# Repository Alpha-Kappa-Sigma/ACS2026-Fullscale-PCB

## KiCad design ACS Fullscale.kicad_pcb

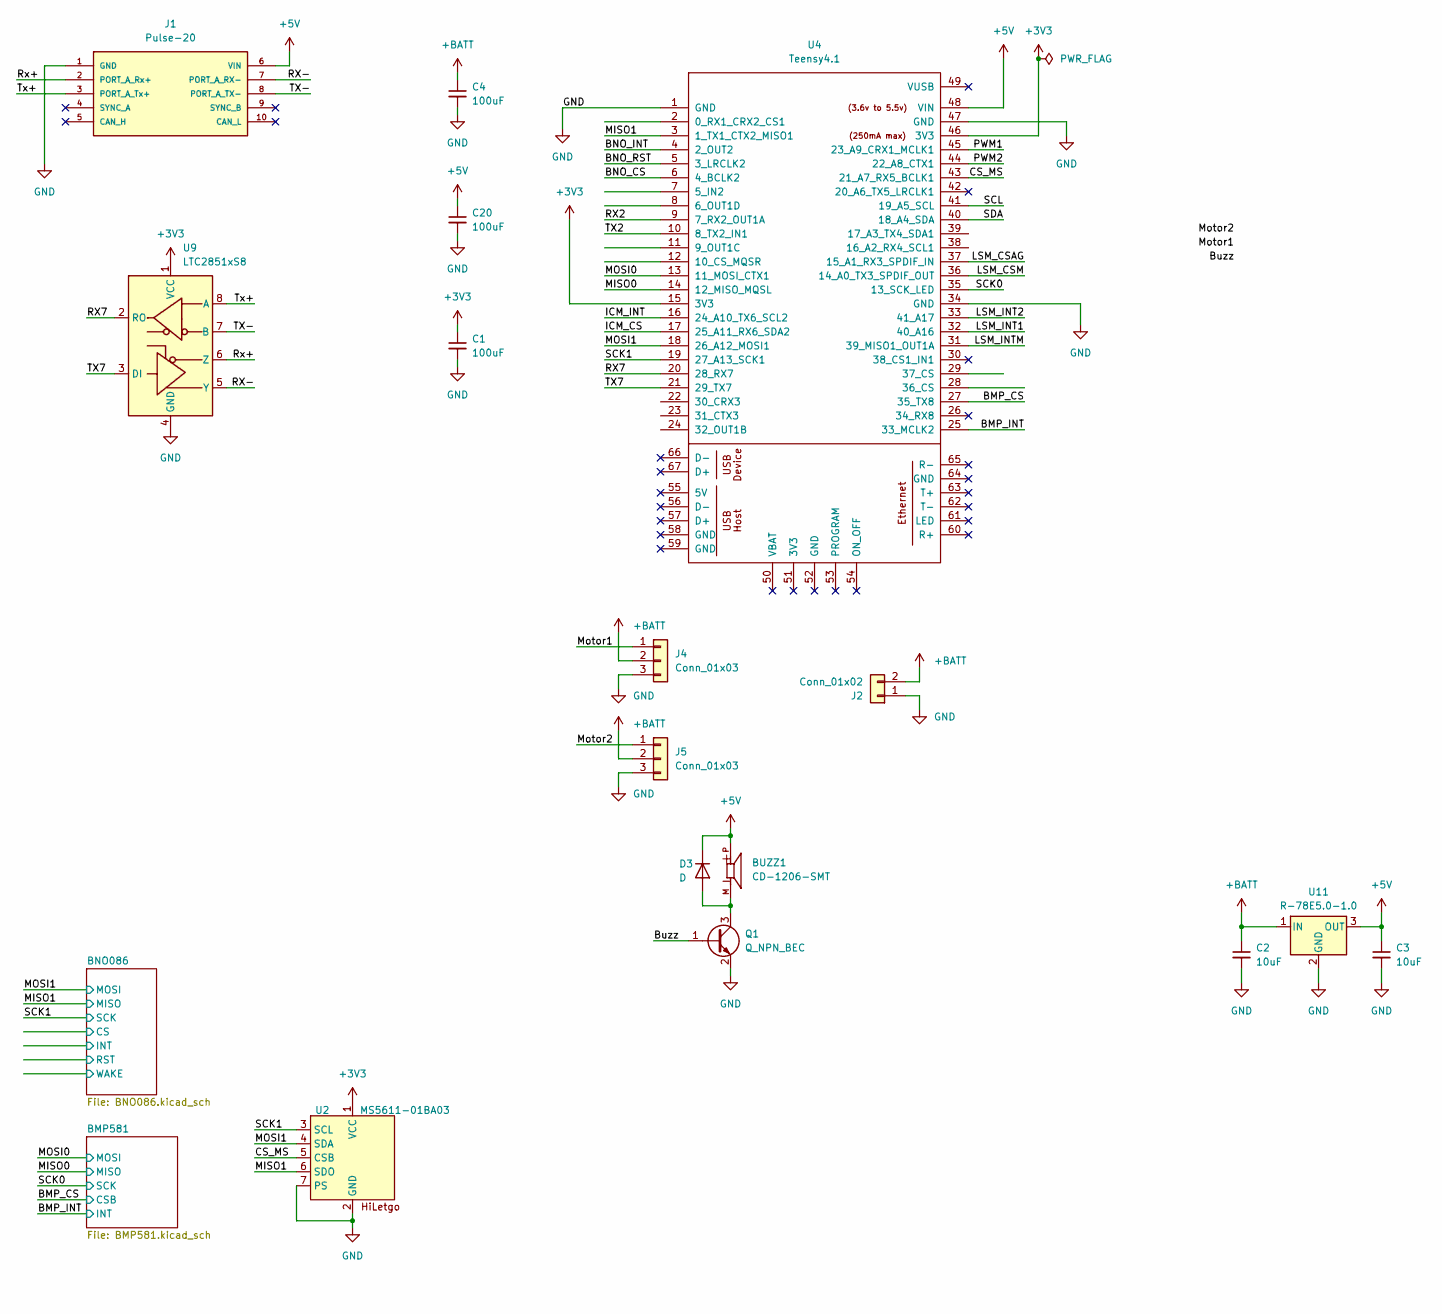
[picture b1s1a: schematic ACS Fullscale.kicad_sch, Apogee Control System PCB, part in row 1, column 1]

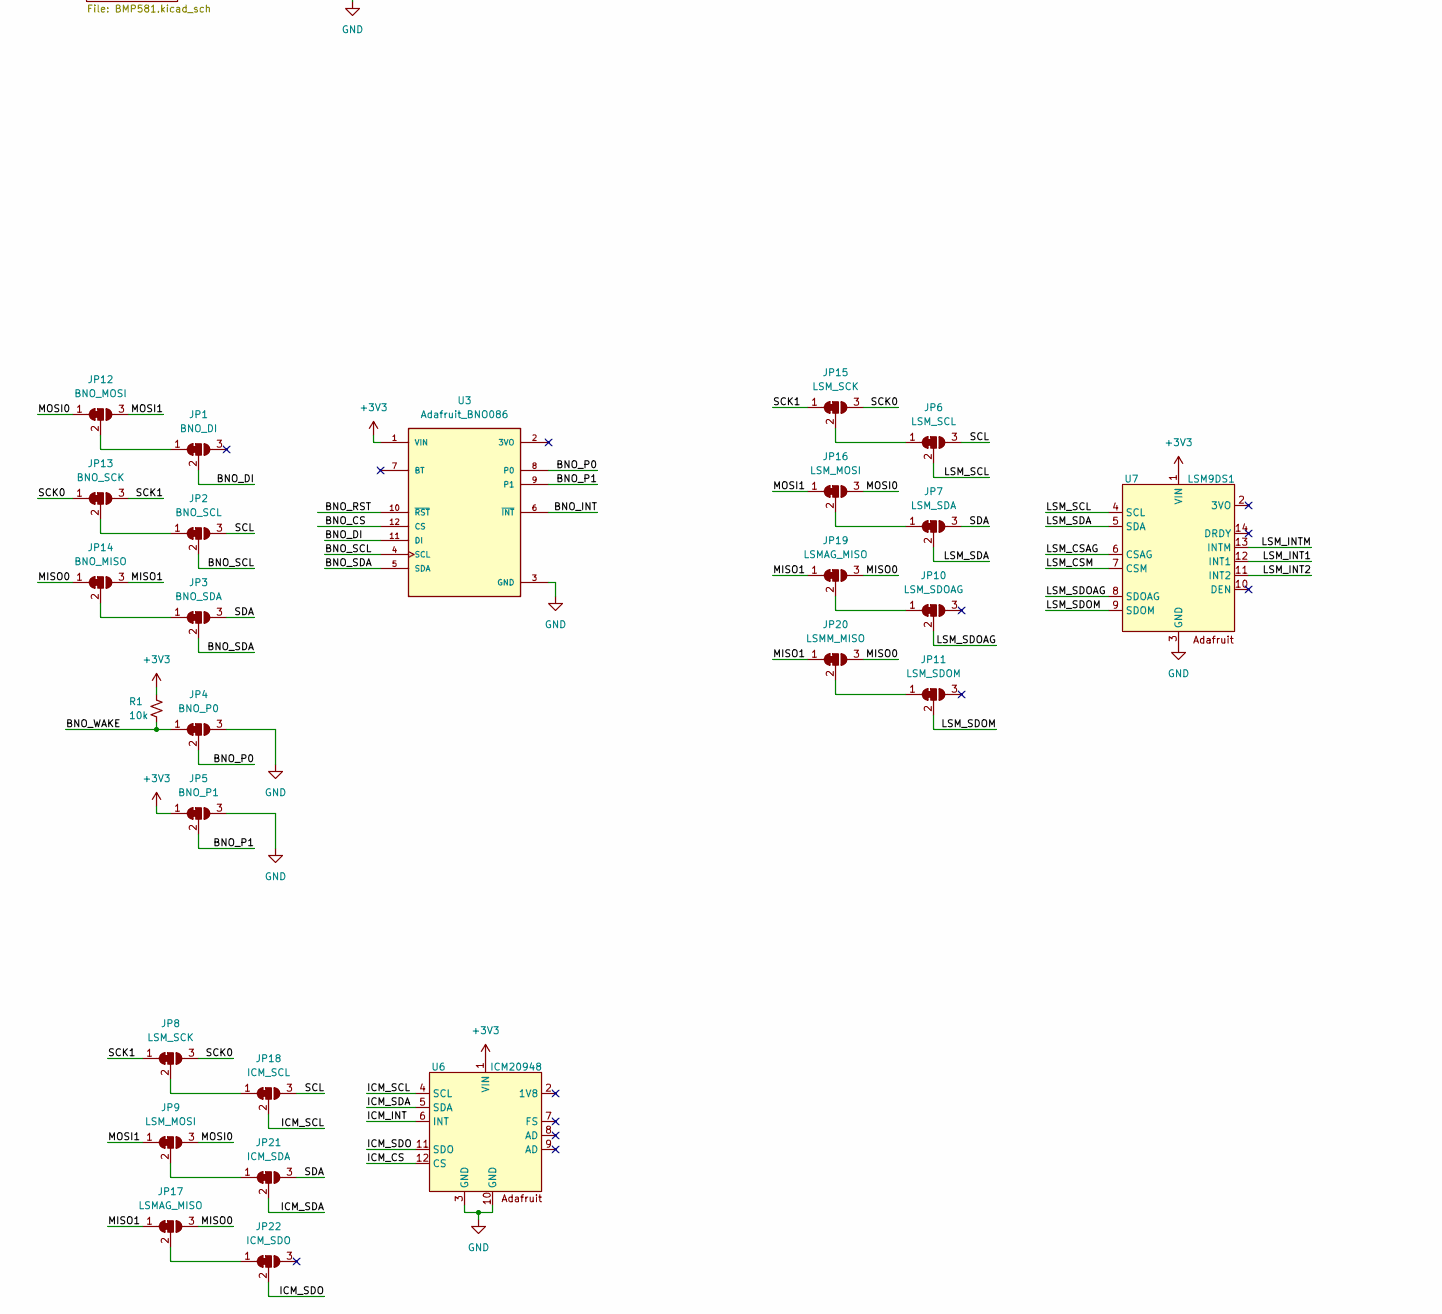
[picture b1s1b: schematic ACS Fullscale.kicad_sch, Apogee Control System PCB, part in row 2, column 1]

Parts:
BUZZ1: CD-1206-SMT; CUI_CD-1206-SMT; DigiKey_Part_Number 102-1150-ND
C1, C4, C20: 100uF; C_1206_3216Metric
C2, C3: 10uF; C_0603_1608Metric
D3: D; D_SOD-323
J1: Pulse-20
J2: Conn_01x02; AMASS_XT30U-M_1x02_P5.0mm_Vertical
J4, J5: Conn_01x03; PinHeader_1x03_P2.54mm_Vertical
JP1: BNO_DI; SolderJumper-3_P1.3mm_Bridged2Bar12_RoundedPad1.0x1.5mm
JP2: BNO_SCL; SolderJumper-3_P1.3mm_Bridged2Bar12_RoundedPad1.0x1.5mm
JP3: BNO_SDA; SolderJumper-3_P1.3mm_Bridged2Bar12_RoundedPad1.0x1.5mm
JP4: BNO_P0; SolderJumper-3_P1.3mm_Bridged2Bar12_RoundedPad1.0x1.5mm
JP5: BNO_P1; SolderJumper-3_P1.3mm_Bridged2Bar12_RoundedPad1.0x1.5mm
JP6: LSM_SCL; SolderJumper-3_P1.3mm_Bridged2Bar12_RoundedPad1.0x1.5mm
JP7: LSM_SDA; SolderJumper-3_P1.3mm_Bridged2Bar12_RoundedPad1.0x1.5mm
JP8, JP15: LSM_SCK; SolderJumper-3_P1.3mm_Bridged2Bar12_RoundedPad1.0x1.5mm
JP9, JP16: LSM_MOSI; SolderJumper-3_P1.3mm_Bridged2Bar12_RoundedPad1.0x1.5mm
JP10: LSM_SDOAG; SolderJumper-3_P1.3mm_Bridged2Bar12_RoundedPad1.0x1.5mm
JP11: LSM_SDOM; SolderJumper-3_P1.3mm_Bridged2Bar12_RoundedPad1.0x1.5mm
JP12: BNO_MOSI; SolderJumper-3_P1.3mm_Bridged2Bar12_RoundedPad1.0x1.5mm
JP13: BNO_SCK; SolderJumper-3_P1.3mm_Bridged2Bar12_RoundedPad1.0x1.5mm
JP14: BNO_MISO; SolderJumper-3_P1.3mm_Bridged2Bar12_RoundedPad1.0x1.5mm
JP17, JP19: LSMAG_MISO; SolderJumper-3_P1.3mm_Bridged2Bar12_RoundedPad1.0x1.5mm
JP18: ICM_SCL; SolderJumper-3_P1.3mm_Bridged2Bar12_RoundedPad1.0x1.5mm
JP20: LSMM_MISO; SolderJumper-3_P1.3mm_Bridged2Bar12_RoundedPad1.0x1.5mm
JP21: ICM_SDA; SolderJumper-3_P1.3mm_Bridged2Bar12_RoundedPad1.0x1.5mm
JP22: ICM_SDO; SolderJumper-3_P1.3mm_Bridged2Bar12_RoundedPad1.0x1.5mm
Q1: Q_NPN_BEC; TSOT-23
R1: 10k; R_0805_2012Metric_Pad1.20x1.40mm_HandSolder
U2: MS5611-01BA03; HiLetgo MS5611
U3: Adafruit_BNO086; Adafruit BNO086; PARTREV 2021-03-16
U4: Teensy4.1; Teensy41
U6: ICM20948; Adafruit ICM20948
U7: LSM9DS1; Adafruit LSM9DS1
U9: LTC2851xS8; SOIC-8_3.9x4.9mm_P1.27mm
U11: R-78E5.0-1.0; Converter_DCDC_RECOM_R-78E-0.5_THT

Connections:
+3V3: C1.1, JP5.1 (A), R1.2, U2.1 (VCC), U3.1 (VIN), U4.15 (3V3), U4.46 (3V3), U6.1 (VIN), U7.1 (VIN), U9.1 (VCC); also elsewhere on the board
+5V: BUZZ1.P, C3.1, C20.1, D3.1 (K), J1.6 (VIN), U4.48 (VIN), U11.3 (OUT)
+BATT: C2.1, C4.1, J2.2, J4.2, J5.2, U11.1 (IN)
/BMP_CS: U4.27 (35_TX8); also elsewhere on the board
/BMP_INT: U4.25 (33_MCLK2); also elsewhere on the board
/BNO_CS: U3.12 (CS), U4.6 (4_BCLK2)
/BNO_DI: JP1.2 (C), U3.11 (DI)
/BNO_INT: U3.6 (~INT), U4.4 (2_OUT2)
/BNO_P0: JP4.2 (C), U3.8 (P0)
/BNO_P1: JP5.2 (C), U3.9 (P1)
/BNO_RST: U3.10 (~RST), U4.5 (3_LRCLK2)
/BNO_SCL: JP2.2 (C), U3.4 (SCL)
/BNO_SDA: JP3.2 (C), U3.5 (SDA)
/BNO_WAKE: JP4.1 (A), R1.1
/Buzz: Q1.1 (B)
/CS_MS: U2.5 (CSB), U4.43 (21_A7_RX5_BCLK1)
/ICM_CS: U4.17 (25_A11_RX6_SDA2), U6.12 (CS)
/ICM_INT: U4.16 (24_A10_TX6_SCL2), U6.6 (INT)
/ICM_SCL: JP18.2 (C), U6.4 (SCL)
/ICM_SDA: JP21.2 (C), U6.5 (SDA)
/ICM_SDO: JP22.2 (C), U6.11 (SDO)
/LSM_CSAG: U4.37 (15_A1_RX3_SPDIF_IN), U7.6 (CSAG)
/LSM_CSM: U4.36 (14_A0_TX3_SPDIF_OUT), U7.7 (CSM)
/LSM_INT1: U4.32 (40_A16), U7.12 (INT1)
/LSM_INT2: U4.33 (41_A17), U7.11 (INT2)
/LSM_INTM: U4.31 (39_MISO1_OUT1A), U7.13 (INTM)
/LSM_SCL: JP6.2 (C), U7.4 (SCL)
/LSM_SDA: JP7.2 (C), U7.5 (SDA)
/LSM_SDOAG: JP10.2 (C), U7.8 (SDOAG)
/LSM_SDOM: JP11.2 (C), U7.9 (SDOM)
/MISO0: JP14.1 (A), JP17.3 (B), JP19.3 (B), JP20.3 (B), U4.14 (12_MISO_MQSL); also elsewhere on the board
/MISO1: JP14.3 (B), JP17.1 (A), JP19.1 (A), JP20.1 (A), U2.6 (SDO), U4.3 (1_TX1_CTX2_MISO1)
/MOSI0: JP9.3 (B), JP12.1 (A), JP16.3 (B), U4.13 (11_MOSI_CTX1); also elsewhere on the board
/MOSI1: JP9.1 (A), JP12.3 (B), JP16.1 (A), U2.4 (SDA), U4.18 (26_A12_MOSI1)
/Motor1: J4.1
/Motor2: J5.1
/PWM1: U4.45 (23_A9_CRX1_MCLK1)
/PWM2: U4.44 (22_A8_CTX1)
/RX2: U4.9 (7_RX2_OUT1A)
/RX7: U4.20 (28_RX7), U9.2 (RO)
/RX-: J1.7 (PORT_A_RX-), U9.5 (Y)
/Rx+: J1.2 (PORT_A_Rx+), U9.6 (Z)
/SCK0: JP8.3 (B), JP13.1 (A), JP15.3 (B), U4.35 (13_SCK_LED); also elsewhere on the board
/SCK1: JP8.1 (A), JP13.3 (B), JP15.1 (A), U2.3 (SCL), U4.19 (27_A13_SCK1)
/SCL: JP2.3 (B), JP6.3 (B), JP18.3 (B), U4.41 (19_A5_SCL)
/SDA: JP3.3 (B), JP7.3 (B), JP21.3 (B), U4.40 (18_A4_SDA)
/TX2: U4.10 (8_TX2_IN1)
/TX7: U4.21 (29_TX7), U9.3 (DI)
/TX-: J1.8 (PORT_A_TX-), U9.7 (B)
/Tx+: J1.3 (PORT_A_Tx+), U9.8 (A)
GND: C1.2, C2.2, C3.2, C4.2, C20.2, J1.1 (GND), J2.1, J4.3, J5.3, JP4.3 (B), JP5.3 (B), Q1.2 (E), U2.2 (GND), U2.7 (PS), U3.3 (GND), U4.1 (GND), U4.34 (GND), U4.47 (GND), U6.3 (GND), U6.10 (GND), U7.3 (GND), U9.4 (GND), U11.2 (GND); also elsewhere on the board
unnamed: BUZZ1.M, D3.2 (A), Q1.3 (C)
unnamed: JP1.1 (A), JP12.2 (C)
unnamed: JP10.1 (A), JP19.2 (C)
unnamed: JP11.1 (A), JP20.2 (C)
unnamed: JP2.1 (A), JP13.2 (C)
unnamed: JP3.1 (A), JP14.2 (C)
unnamed: JP6.1 (A), JP15.2 (C)
unnamed: JP7.1 (A), JP16.2 (C)
unnamed: JP17.2 (C), JP22.1 (A)
unnamed: JP8.2 (C), JP18.1 (A)
unnamed: JP9.2 (C), JP21.1 (A)

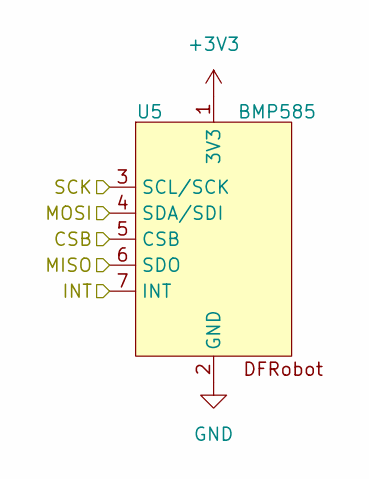
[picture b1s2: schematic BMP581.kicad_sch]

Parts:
U5: BMP585; DFRobot BMP585

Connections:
+3V3: U5.1 (3V3); also elsewhere on the board
/BMP_CS: U5.5 (CSB); also elsewhere on the board
/BMP_INT: U5.7 (INT); also elsewhere on the board
/MISO0: U5.6 (SDO); also elsewhere on the board
/MOSI0: U5.4 (SDA/SDI); also elsewhere on the board
/SCK0: U5.3 (SCL/SCK); also elsewhere on the board
GND: U5.2 (GND); also elsewhere on the board

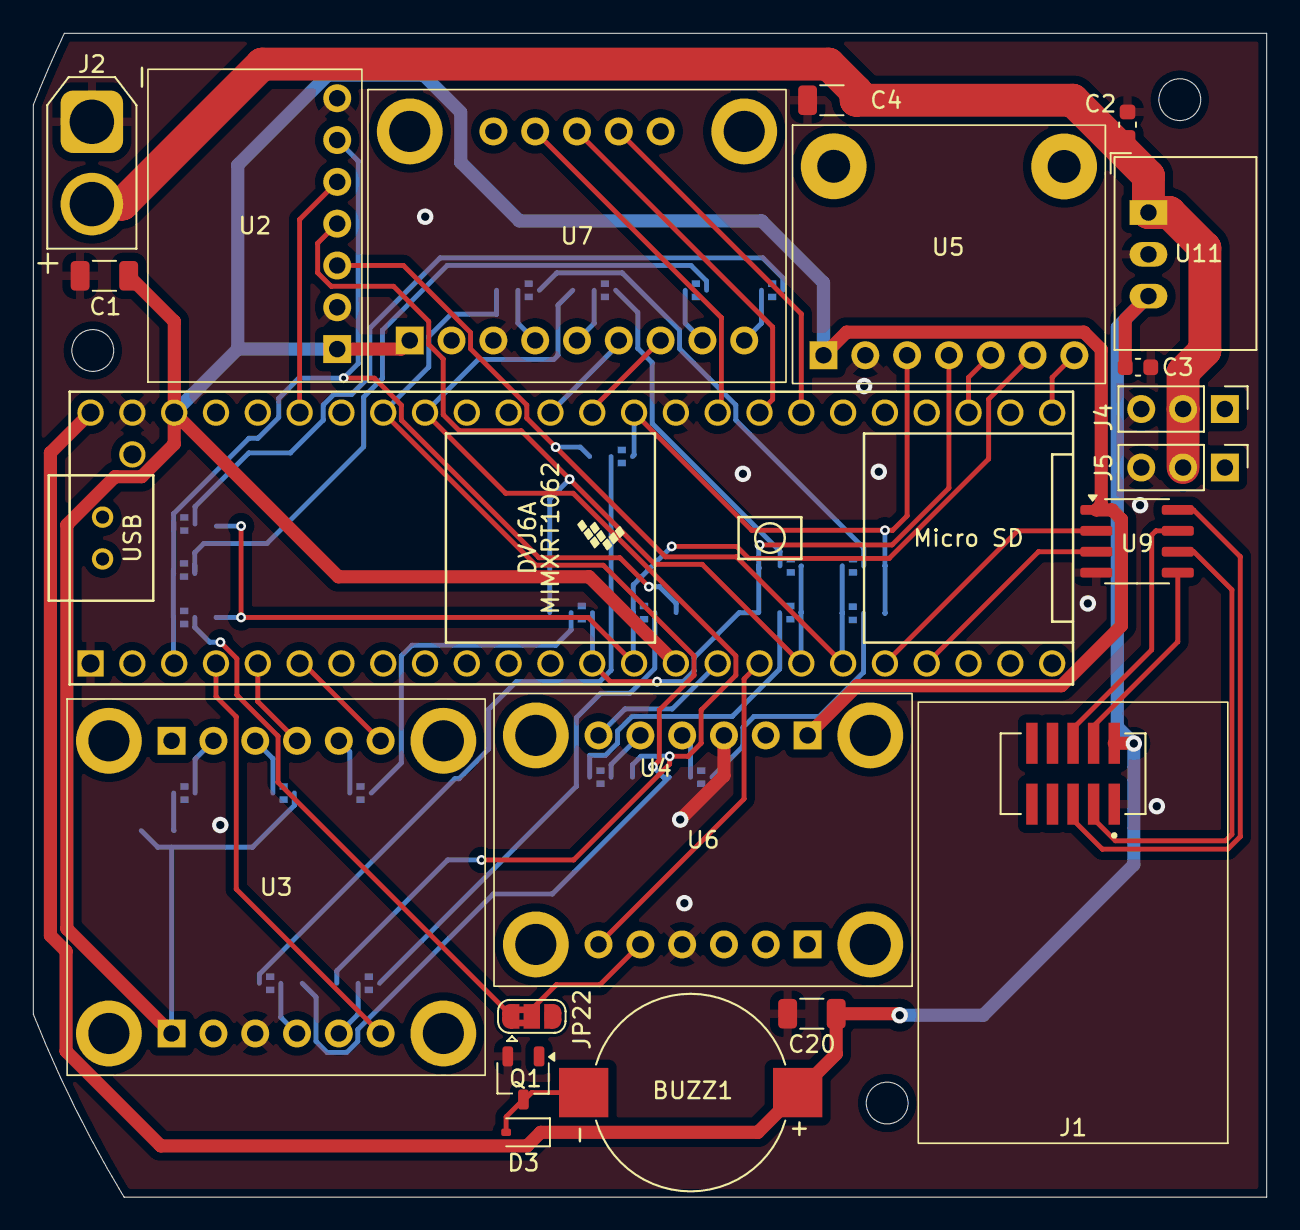
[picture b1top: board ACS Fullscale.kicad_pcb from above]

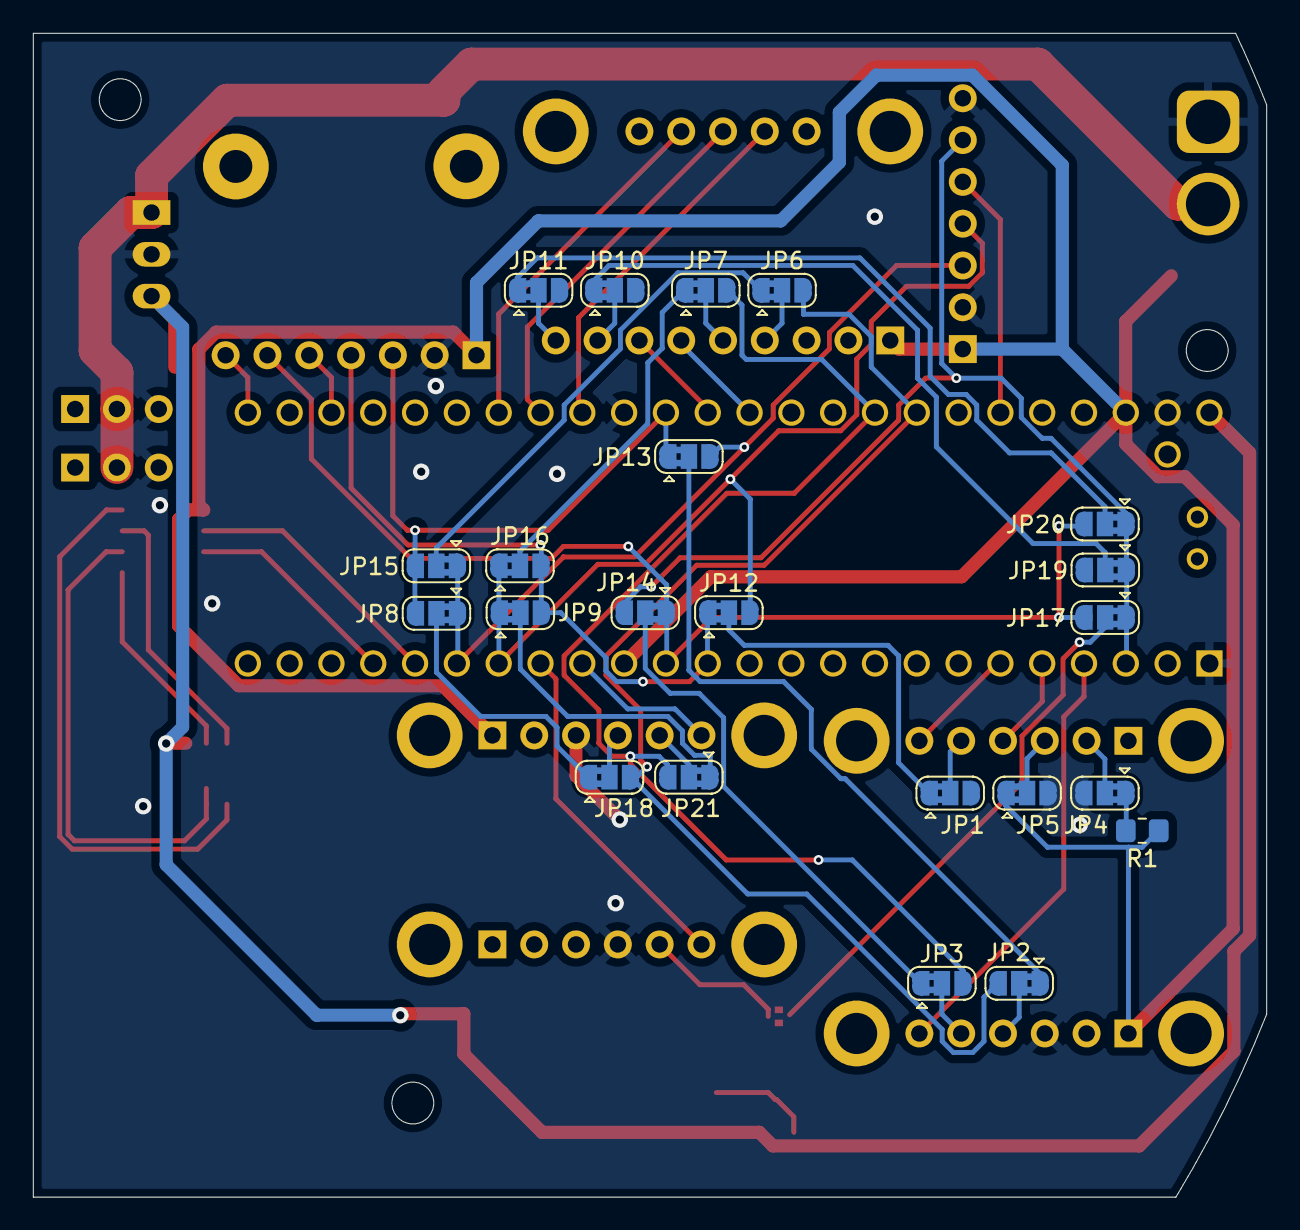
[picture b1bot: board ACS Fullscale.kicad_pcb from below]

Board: 2 copper layers, 74.9 x 70.7 mm, 43 parts (22 on the bottom side), 55 nets.

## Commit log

2025-12-04 This is a test
2025-12-04 Adding subscale
2025-12-04 Wire test
2025-12-07 test
2025-12-10 nothing
2025-12-10 Create test
2025-12-10 libs
2025-12-10 fix lib
2025-12-20 I changed the diameter of the PCB to 5.95 in
2025-12-20 I added the symbols for the CM5 in accordance with https://pip.raspberrypi.com/categories/1098-design-files, including all related files.
2025-12-31 CM5 sutff added
2026-01-04 A lot of stuff
2026-01-19 ryan
2026-02-16 lots
